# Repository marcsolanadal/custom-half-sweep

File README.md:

# Custom keyboard

This keyboard is based on the `Sweep Half Swept` keyboard.

Some of the modifications I did:

- Removed reset button
- Modified PCB shape
- Rerouted most of tracks 
- Solved many CRC warnings (many still there)

Once I have the first prototype and I'm used to using a 36 key I'll improve on the design.

Main features missing:

- Hot-swappable connectors
- Wireless controler Nano!
- Custom shape to my hand
- Wooden case

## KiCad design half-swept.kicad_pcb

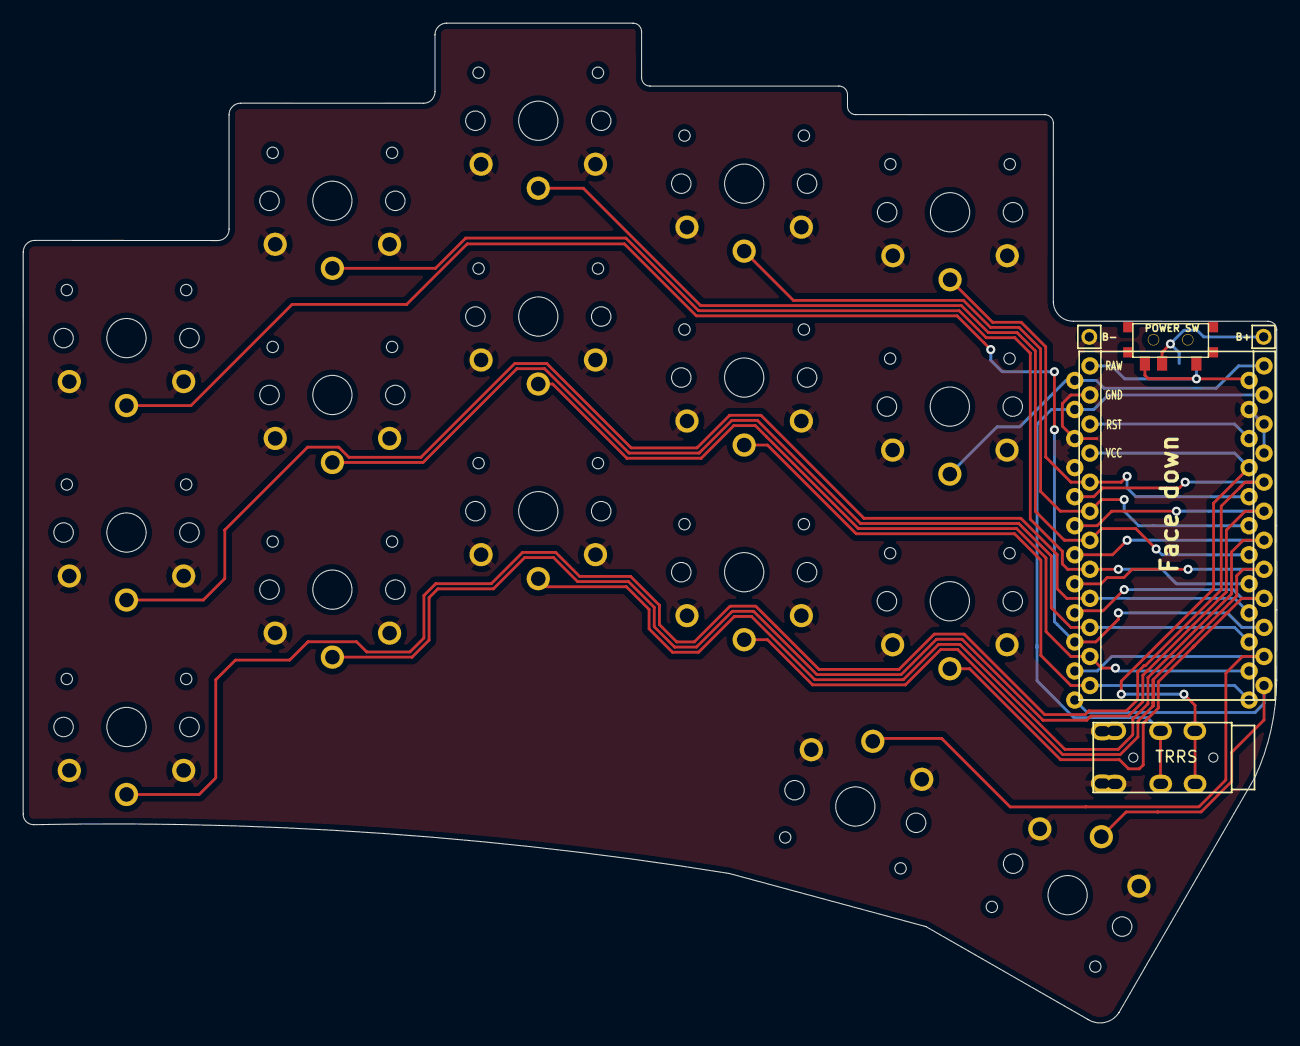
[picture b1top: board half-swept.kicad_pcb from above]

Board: 2 copper layers, 109.6 x 87.4 mm, 23 parts (1 on the bottom side), 22 nets.

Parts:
B+: MountingHole_Pad; 1pin_conn
B-: MountingHole_Pad; 1pin_conn
J2: AudioJack4dpb; TRRS-PJ-DPB2
POWER SW: SW_SPDT; SPDT_C128955
SW2, SW3, SW4, SW5, SW6, SW8, SW9, SW10, SW11, SW12, SW14, SW15, SW16, SW17, SW18, SW20, SW21: SW_Push; SW_PG1350_rev_DPB
SW2#2: SW_SPDT; SPDT_C128955r
U1: ProMicro-kbd; ProMicro_v2

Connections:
BT+_r: B+.1, POWER SW.2, SW2#2.2
Switch1: SW2.1, U1.10
Switch2: SW3.1, U1.17
Switch3: SW4.1, U1.18
Switch4: SW5.1, U1.19
Switch5: SW6.1, U1.20
Switch6: SW8.1, U1.16
Switch7: SW9.1, U1.15
Switch8: SW10.1, U1.14
Switch9: SW11.1, U1.13
Switch10: SW12.1, U1.1
Switch11: SW14.1, U1.5
Switch12: SW15.1, U1.6
Switch13: SW16.1, U1.7
Switch14: SW17.1, U1.8
Switch15: SW18.1, U1.9
Switch16: SW21.1, U1.11
Switch17: SW20.1, U1.12
Switch18: J2.R1, U1.2
gnd: B-.1, J2.S, J2.T, SW2.2, SW3.2, SW4.2, SW5.2, SW6.2, SW8.2, SW9.2, SW10.2, SW11.2, SW12.2, SW14.2, SW15.2, SW16.2, SW17.2, SW18.2, SW20.2, SW21.2, U1.3, U1.4, U1.23
raw: POWER SW.3, SW2#2.3, U1.24
vcc: J2.R2, U1.21

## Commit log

2022-03-19 First prototype design
2022-03-27 initial commit with first prototype
